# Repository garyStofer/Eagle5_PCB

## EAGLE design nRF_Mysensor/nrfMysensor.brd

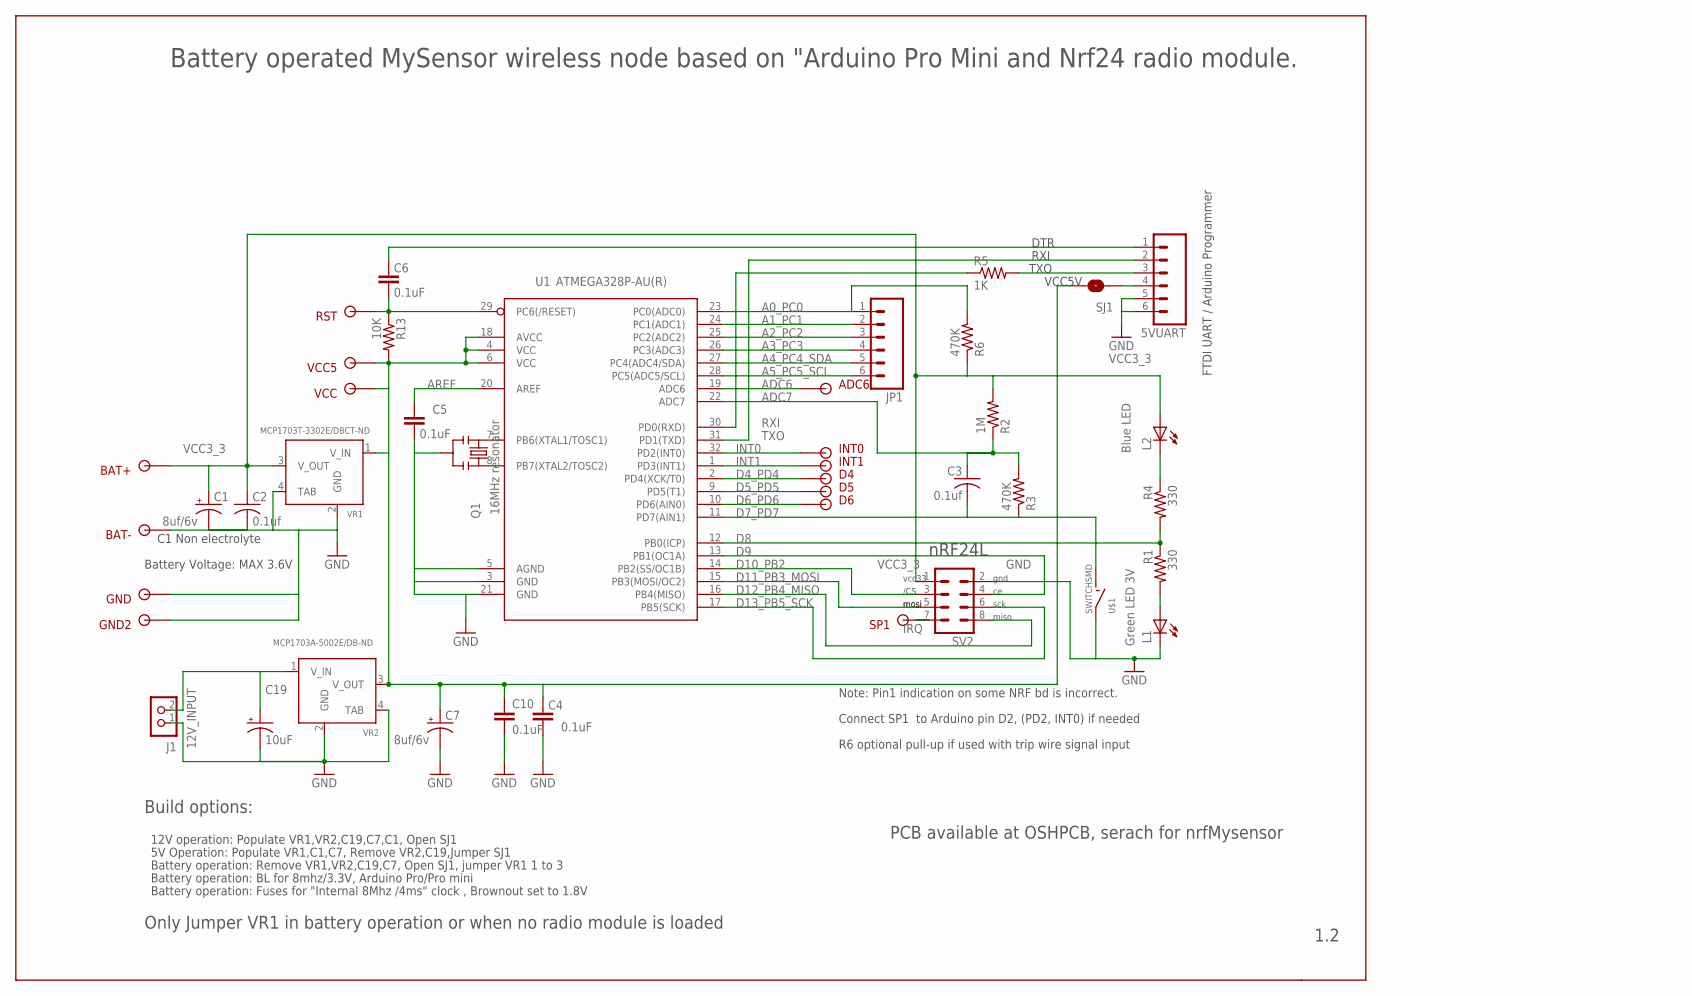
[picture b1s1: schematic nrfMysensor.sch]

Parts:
5VUART: M06SIP; 1X06
ADC6: SOLDER_POINTA; P1-13
BAT+: SOLDER_POINTA; P1-13
BAT-: SOLDER_POINTA; P1-13
C1, C7: 8uf/6v; SMC_B
C2, C3: 0.1uf; C0805
C4, C5, C6, C10: 0.1uF; 0805
C19: 10uF; EIA7343
D4, D5, D6: SOLDER_POINTA; P1-13
GND, GND2: SOLDER_POINTA; P1-13
INT0, INT1: SOLDER_POINTA; P1-13
J1: 12V input; M1X2
JP1: M06SIP; 1X06
L1, L2: LEDSML0603; SML0603
Q1: 16MHz resonator; RESONATOR-SMD
R1, R4: 330; R0603
R2: 1M; R0603
R3, R6: 470K; R0603
R5: 1K; 0603
R13: 10K; 0603
RST: SOLDER_POINTA; P1-13
SJ1: SOLDERJUMPERNO; SJ_2S-NO
SP1: SOLDER_POINTA; P1-13
SV2: MA04-2
U1: ATMEGA328P-AU(R); TQFP32-08
U$1: SWITCHSMD; SMD_SWITCH
VCC, VCC5: SOLDER_POINTA; P1-13
VR1: MCP1703T-3302E/DBCT-ND; SOT223
VR2: MCP1703A-5002E/DB-ND; SOT223

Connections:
5V: C4.2, C7.+, C10.1, R13.2, SJ1.1, U1.4 (VCC), U1.6 (VCC), U1.18 (AVCC), VCC.1, VCC5.1, VR1.1 (V_IN), VR2.3 (V_OUT)
12V_INPUT: C19.A (+), J1.2, VR2.1 (V_IN)
A0_PC0: JP1.1, R6.2, U1.23 (PC0(ADC0))
A1_PC1: JP1.2, U1.24 (PC1(ADC1))
A2_PC2: JP1.3, U1.25 (PC2(ADC2))
A3_PC3: JP1.4, U1.26 (PC3(ADC3))
A4_PC4_SDA: JP1.5, U1.27 (PC4(ADC4/SDA))
A5_PC5_SCL: JP1.6, U1.28 (PC5(ADC5/SCL))
ADC6: ADC6.1, U1.19 (ADC6)
ADC7: C3.1, R2.1, R3.2, U1.22 (ADC7)
AREF: C5.2, U1.20 (AREF)
D4_PD4: D4.1, U1.2 (PD4(XCK/T0))
D5_PD5: D5.1, U1.9 (PD5(T1))
D6_PD6: D6.1, U1.10 (PD6(AIN0))
D7_PD7: C3.2, R3.1, U1.11 (PD7(AIN1)), U$1.P$1
D8: R1.1, R4.2, U1.12 (PB0(ICP))
D9: SV2.4, U1.13 (PB1(OC1A))
D10_PB2: SV2.3, U1.14 (PB2(SS/OC1B))
D11_PB3_MOSI: SV2.5, U1.15 (PB3(MOSI/OC2))
D12_PB4_MISO: SV2.8, U1.16 (PB4(MISO))
D13_PB5_SCK: SV2.6, U1.17 (PB5(SCK))
GND: 5VUART.5, 5VUART.6, BAT-.1, C1.-, C2.2, C4.1, C5.1, C7.-, C10.2, C19.C (-), GND.1, GND2.1, J1.1, L1.C, Q1.2, SV2.2, U1.3 (GND), U1.5 (AGND), U1.21 (GND), U$1.P$2, VR1.2 (GND), VR1.4 (TAB), VR2.2 (GND), VR2.4 (TAB)
INT0: INT0.1, U1.32 (PD2(INT0))
INT1: INT1.1, U1.1 (PD3(INT1))
IRQ: SP1.1, SV2.7
unnamed: L1.A, R1.2
unnamed: L2.C, R4.1
unnamed: 5VUART.3, R5.2
unnamed: 5VUART.4, SJ1.2
unnamed: Q1.1, U1.8 (PB7(XTAL2/TOSC2))
unnamed: 5VUART.1, C6.2
unnamed: Q1.3, U1.7 (PB6(XTAL1/TOSC1))
RESET: C6.1, R13.1, RST.1, U1.29 (PC6(/RESET))
RXI: R5.1, U1.30 (PD0(RXD))
TXO: 5VUART.2, U1.31 (PD1(TXD))
VCC3_3: BAT+.1, C1.+, C2.1, L2.A, R2.2, R6.1, SV2.1, VR1.3 (V_OUT)

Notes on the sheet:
nRF24L
Blue LED
Green LED 3V
Connect SP1 to Arduino pin D2, (PD2, INT0) if needed
Note: Pin1 indication on some NRF bd is incorrect.
/CS
mosi
miso
sck
gnd
vcc33
Battery Voltage: MAX 3.6V
FTDI UART / Arduino Programmer
C1 Non electrolyte
TXO
RXI
VCC5V
DTR
5V Operation: Populate VR1,C1,C7, Remove VR2,C19,Jumper SJ1
12V operation: Populate VR1,VR2,C19,C7,C1, Open SJ1
Battery operation: Remove VR1,VR2,C19,C7, Open SJ1, jumper VR1 1 to 3
Battery operation: BL for 8mhz/3.3V, Arduino Pro/Pro mini
Battery operation: Fuses for "Internal 8Mhz /4ms" clock , Brownout set to 1.8V
1.2
Battery operated MySensor wireless node based on "Arduino Pro Mini and Nrf24 radio module.
Build options:
PCB available at OSHPCB, serach for nrfMysensor
Only Jumper VR1 in battery operation or when no radio module is loaded
R6 optional pull-up if used with trip wire signal input

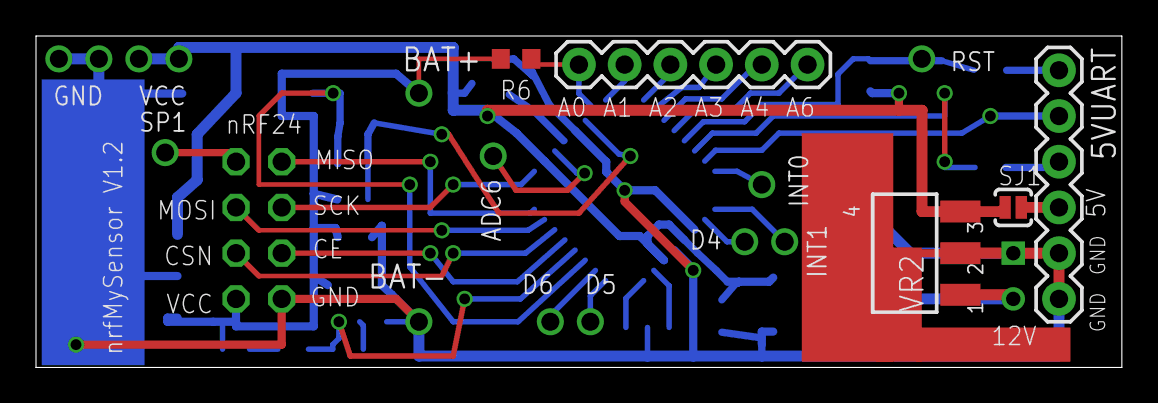
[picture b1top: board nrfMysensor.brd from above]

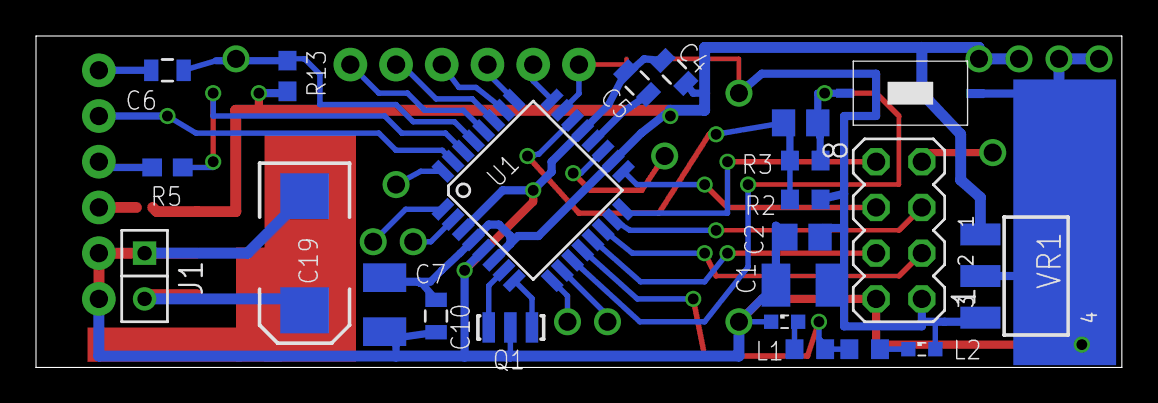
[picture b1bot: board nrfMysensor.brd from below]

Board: 2 copper layers, 60.3 x 18.4 mm, 42 parts (23 on the bottom side), 36 nets.

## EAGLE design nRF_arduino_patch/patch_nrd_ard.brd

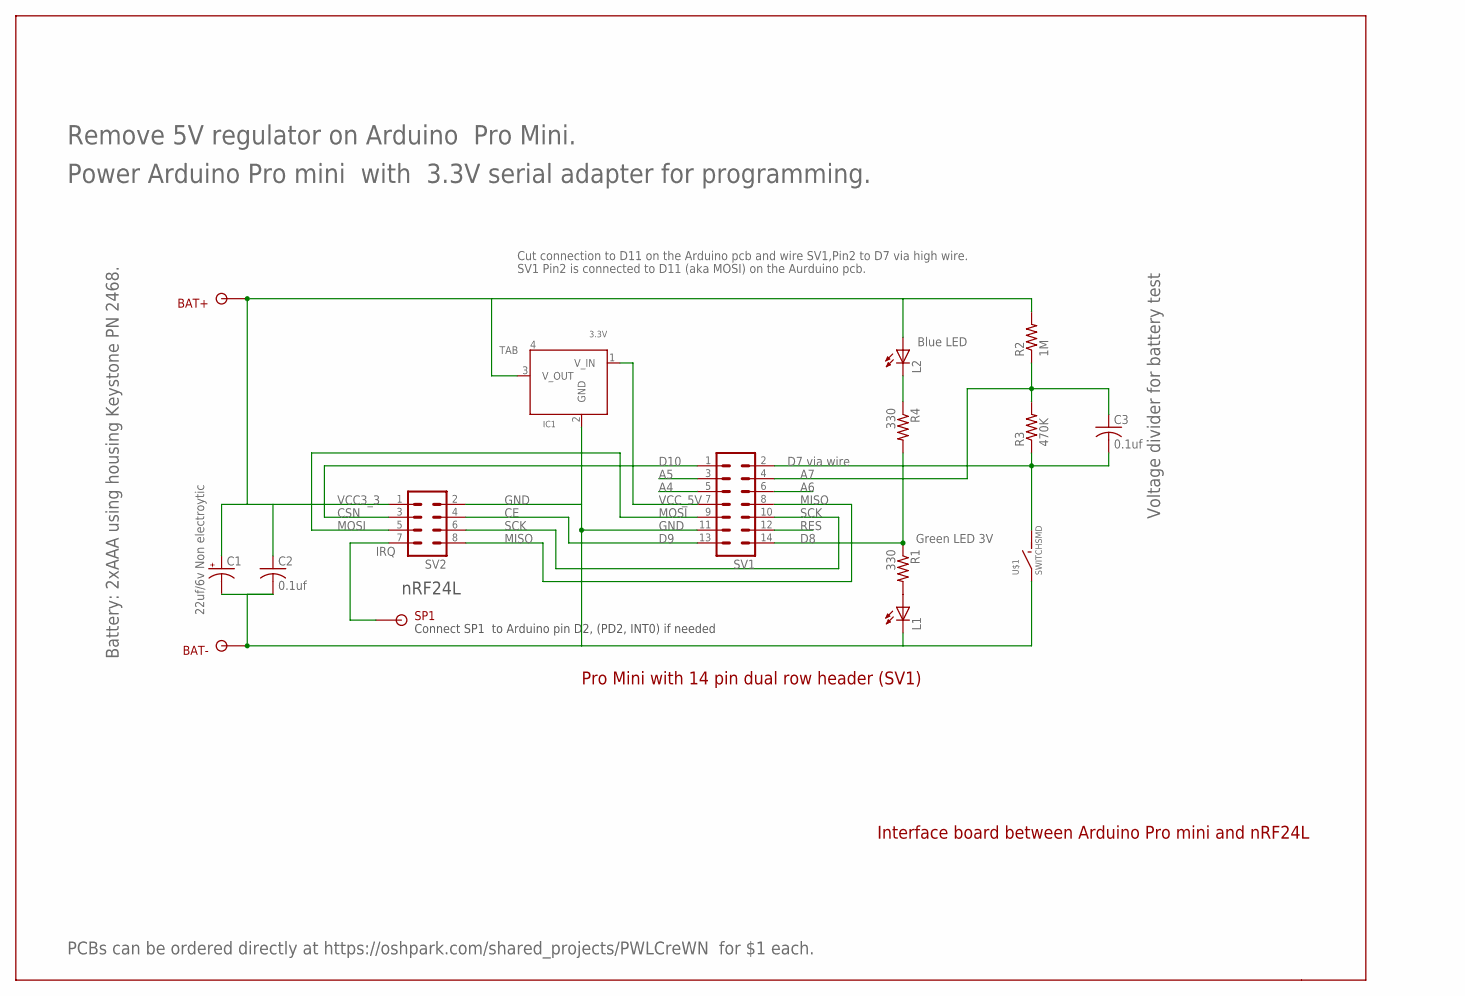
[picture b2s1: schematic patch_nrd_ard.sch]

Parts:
BAT+: SOLDER_POINTA; P1-13
BAT-: SOLDER_POINTA; P1-13
C1: 22uf/6v Non electroytic; SMC_B
C2, C3: 0.1uf; C0805
IC1: 3.3V; SOT223
L1, L2: LEDSML0603; SML0603
R1, R4: 330; R0603
R2: 1M; R0603
R3: 470K; R0603
SP1: SOLDER_POINTA; P1-13
SV1: MA07-2
SV2: MA04-2
U$1: SWITCHSMD; SMD_SWITCH

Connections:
A4: SV1.5
A5: SV1.3
A6: SV1.6
A7: C3.1, R2.1, R3.2, SV1.4
CE: SV1.13, SV2.4
CSN: SV1.1, SV2.3
D8: R1.1, R4.2, SV1.14
D11: C3.2, R3.1, SV1.2, U$1.P$1
GND: BAT-.1, C1.-, C2.2, IC1.2 (GND), L1.C, SV1.11, SV2.2, U$1.P$2
IRQ: SP1.1, SV2.7
MISO: SV1.8, SV2.8
MOSI: SV1.9, SV2.5
unnamed: L1.A, R1.2
unnamed: L2.C, R4.1
RES: SV1.12
SCK: SV1.10, SV2.6
VCC3_3: BAT+.1, C1.+, C2.1, IC1.3 (V_OUT), L2.A, R2.2, SV2.1
VCC_5V: IC1.1 (V_IN), SV1.7

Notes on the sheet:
D10
D7 via wire
Interface board between Arduino Pro mini and nRF24L
Pro Mini with 14 pin dual row header (SV1)
nRF24L
Voltage divider for battery test
Battery: 2xAAA using housing Keystone PN 2468.
Blue LED
Green LED 3V
Cut connection to D11 on the Arduino pcb and wire SV1,Pin2 to D7 via high wire.
SV1 Pin2 is connected to D11 (aka MOSI) on the Aurduino pcb.
PCBs can be ordered directly at https://oshpark.com/shared_projects/PWLCreWN for $1 each.
Remove 5V regulator on Arduino Pro Mini.
Power Arduino Pro mini with 3.3V serial adapter for programming.
Connect SP1 to Arduino pin D2, (PD2, INT0) if needed

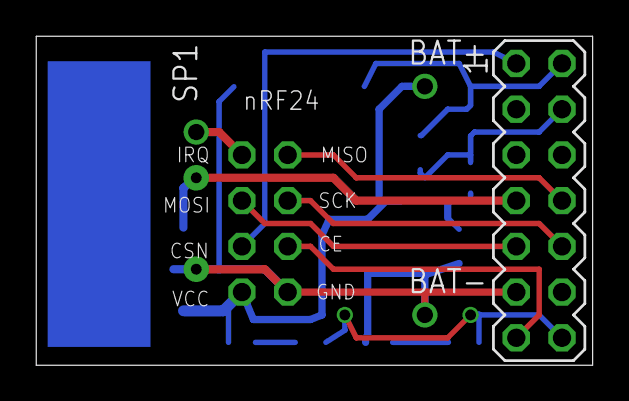
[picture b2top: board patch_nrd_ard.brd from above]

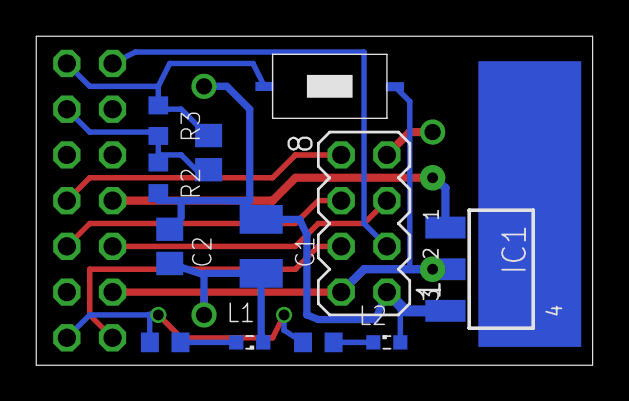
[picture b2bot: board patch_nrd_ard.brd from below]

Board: 2 copper layers, 30.9 x 18.3 mm, 16 parts (12 on the bottom side), 14 nets.

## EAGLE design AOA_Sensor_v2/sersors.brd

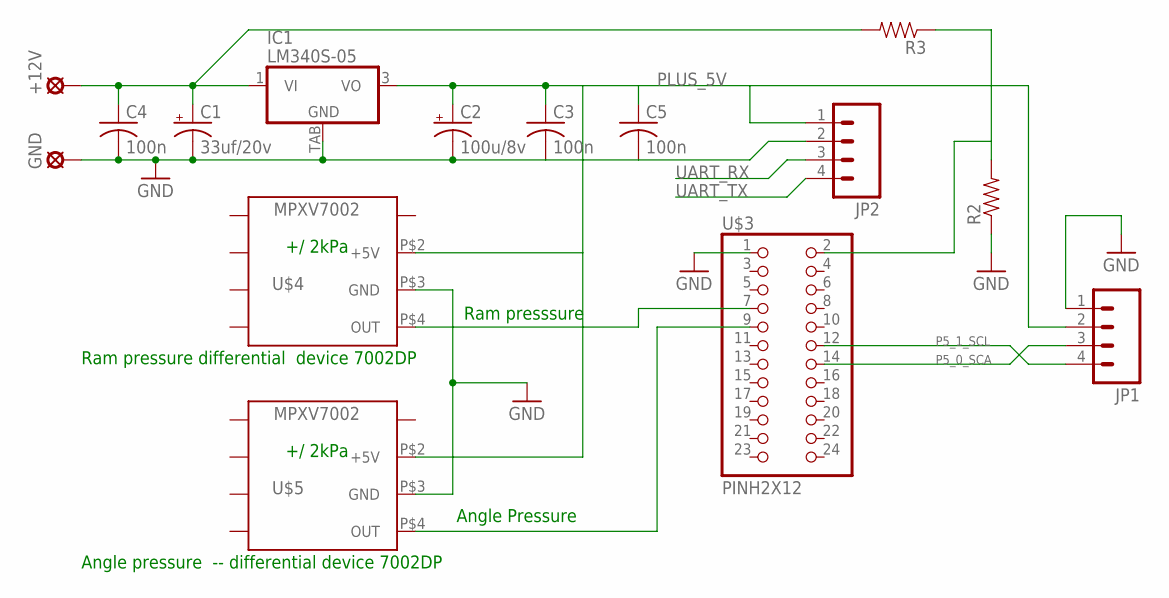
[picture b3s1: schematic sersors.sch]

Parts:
+12V: LSP10
C1: 33uf/20v; SMC_D
C2: 100u/8v; SMC_D
C3, C4, C5: 100n; C1206K
GND: LSP10
IC1: LM340S-05; TO263-3
JP1, JP2: M04PTH; 1X04
R2, R3: RESISTOR0603-RES; 0603-RES
U$3: PINH2X12; 2X12
U$4, U$5: MPXV7002; MPXV

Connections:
GND: C1.-, C2.-, C3.2, C4.2, C5.2, GND.MP, IC1.TAB (GND), JP1.1, JP2.2, R2.1, U$3.1, U$4.P$3 (GND), U$5.P$3 (GND)
unnamed: +12V.MP, C1.+, C4.1, IC1.1 (VI), R3.2
unnamed: U$3.7, U$4.P$4 (OUT)
unnamed: R2.2, R3.1, U$3.2
P3_1: U$3.9, U$5.P$4 (OUT)
P5_0_SCA: JP1.3, U$3.14
P5_1_SCL: JP1.4, U$3.12
PLUS_5V: C2.+, C3.1, C5.1, IC1.3 (VO), JP1.2, JP2.1, U$4.P$2 (+5V), U$5.P$2 (+5V)
UART_RX: JP2.3
UART_TX: JP2.4

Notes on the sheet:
+/ 2kPa
Ram presssure
Angle Pressure
Angle pressure -- differential device 7002DP
Ram pressure differential device 7002DP

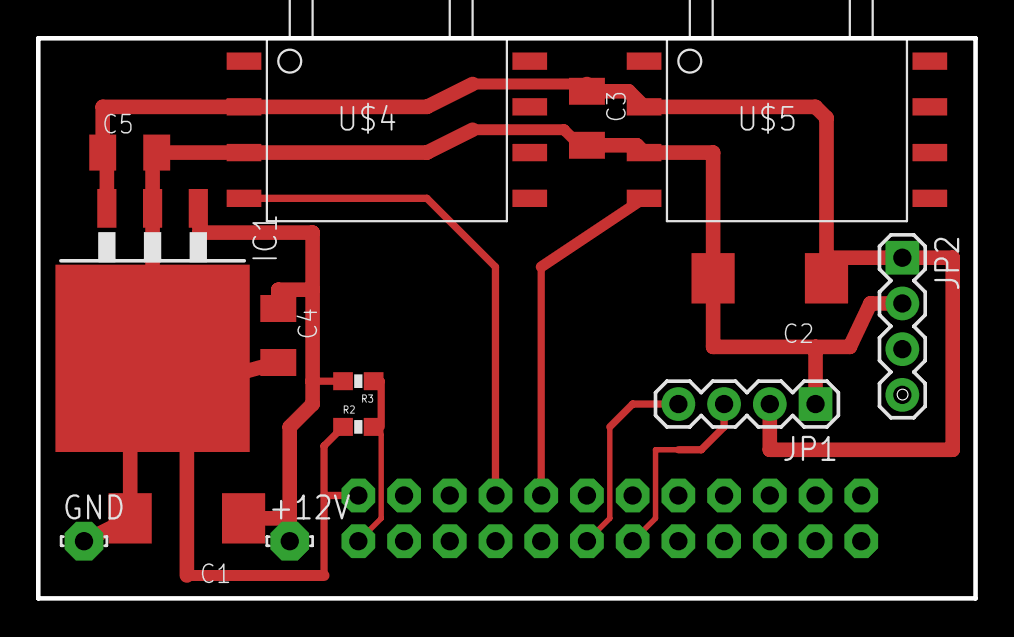
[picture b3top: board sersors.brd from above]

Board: 2 copper layers, 52.1 x 31.1 mm, 15 parts (1 on the bottom side), 8 nets.

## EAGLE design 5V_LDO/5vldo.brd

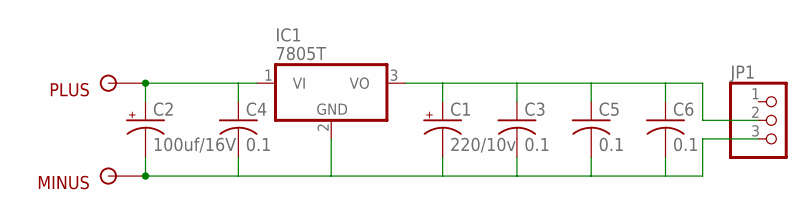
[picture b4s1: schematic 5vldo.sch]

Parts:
C1: 220/10v; SMC_B
C2: 100uf/16V; SMC_B
C3, C4, C5, C6: 0.1; C0805
IC1: 7805T; TO220H
JP1: PINHD-1X3; 1X03
MINUS: SOLDER_POINTD; P1-17Y
PLUS: SOLDER_POINTD; P1-17Y

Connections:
unnamed: C2.+, C4.1, IC1.1 (VI), PLUS.1
unnamed: C1.-, C2.-, C3.2, C4.2, C5.2, C6.2, IC1.2 (GND), JP1.3, MINUS.1
unnamed: C1.+, C3.1, C5.1, C6.1, IC1.3 (VO), JP1.2

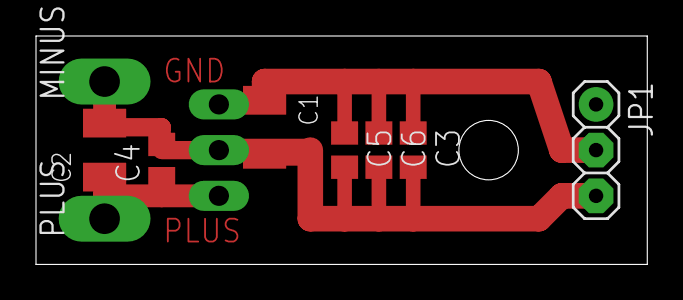
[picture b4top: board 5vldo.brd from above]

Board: 2 copper layers, 34.0 x 12.7 mm, 10 parts (1 on the bottom side), 3 nets.

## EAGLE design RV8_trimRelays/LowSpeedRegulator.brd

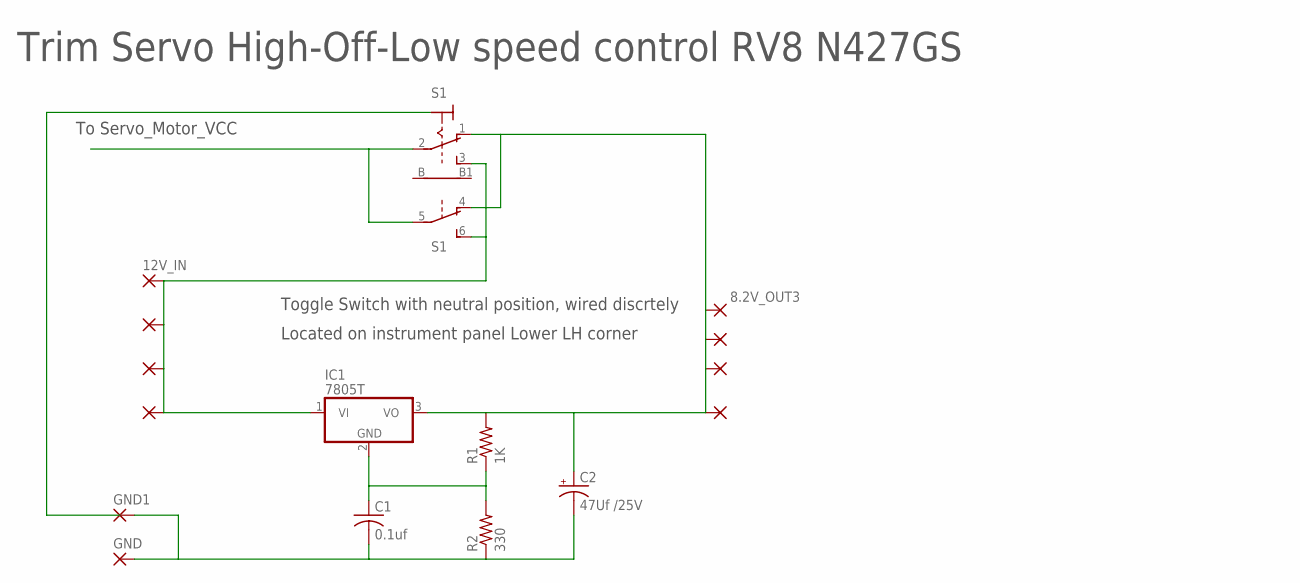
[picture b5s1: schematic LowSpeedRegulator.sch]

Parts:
6V_OUT1, 6V_OUT2, 6V_OUT4, 8.2V_OUT3, 12V, 12V_IN, 12_V, 12_V2: 3,17/1,1
C1: 0.1uf; C0805K
C2: 47Uf /25V; SMC_D
GND, GND1: 3,17/1,1
IC1: 7805T; TO220H
R1: 1K; R0805W
R2: 330; R0805W
S1: 316-923

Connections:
unnamed: C1.1, IC1.2 (GND), R1.1, R2.2
unnamed: C1.2, C2.-, GND.1, GND1.1, R2.1
unnamed: 6V_OUT1.1, 6V_OUT2.1, 6V_OUT4.1, 8.2V_OUT3.1, C2.+, IC1.3 (VO), R1.2, S1.1 (O), S1.4 (O)
unnamed: 12V.1, 12V_IN.1, 12_V.1, 12_V2.1, IC1.1 (VI), S1.3 (S), S1.6 (S)
unnamed: S1.2, S1.5

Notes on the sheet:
To Servo_Motor_VCC
Toggle Switch with neutral position, wired discrtely
Trim Servo High-Off-Low speed control RV8 N427GS
Located on instrument panel Lower LH corner

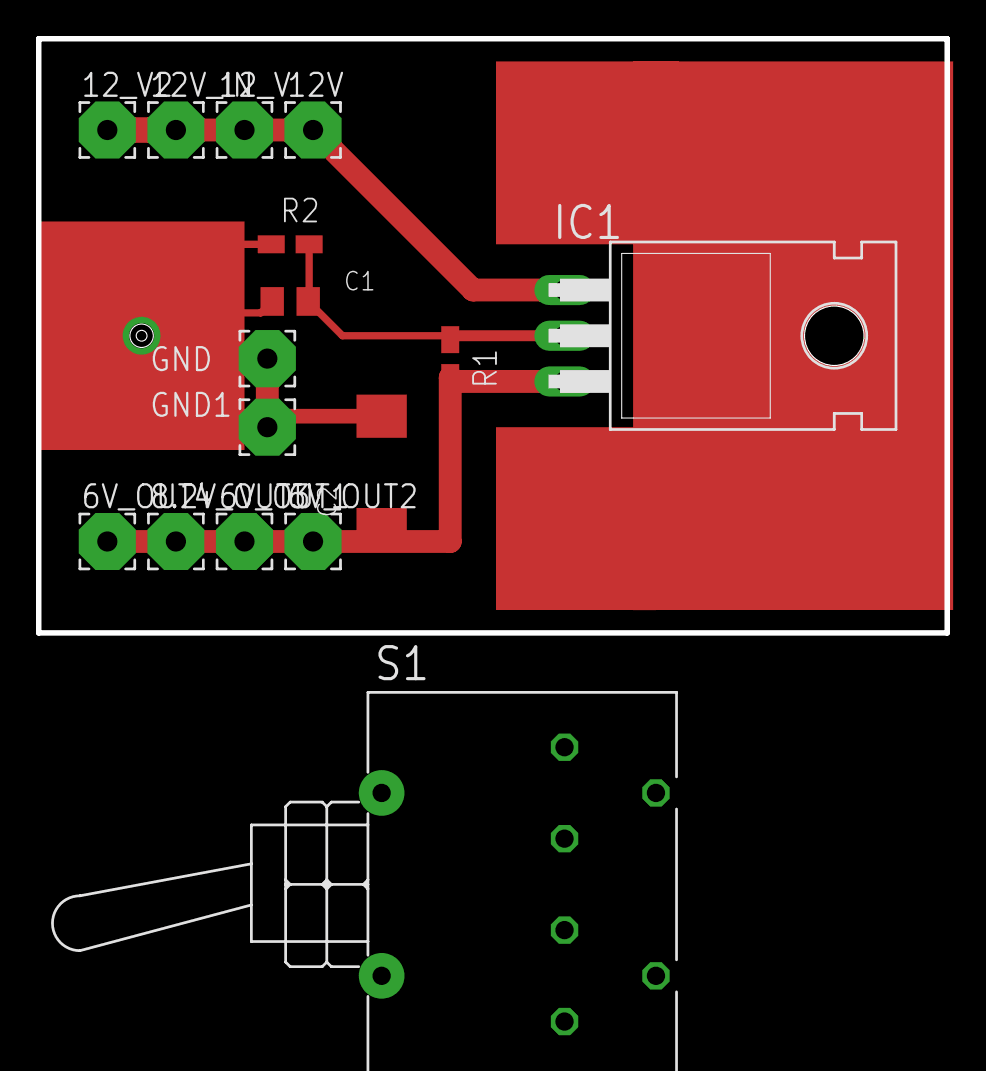
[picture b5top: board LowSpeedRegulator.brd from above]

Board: 2 copper layers, 50.5 x 33.0 mm, 16 parts (0 on the bottom side), 5 nets.

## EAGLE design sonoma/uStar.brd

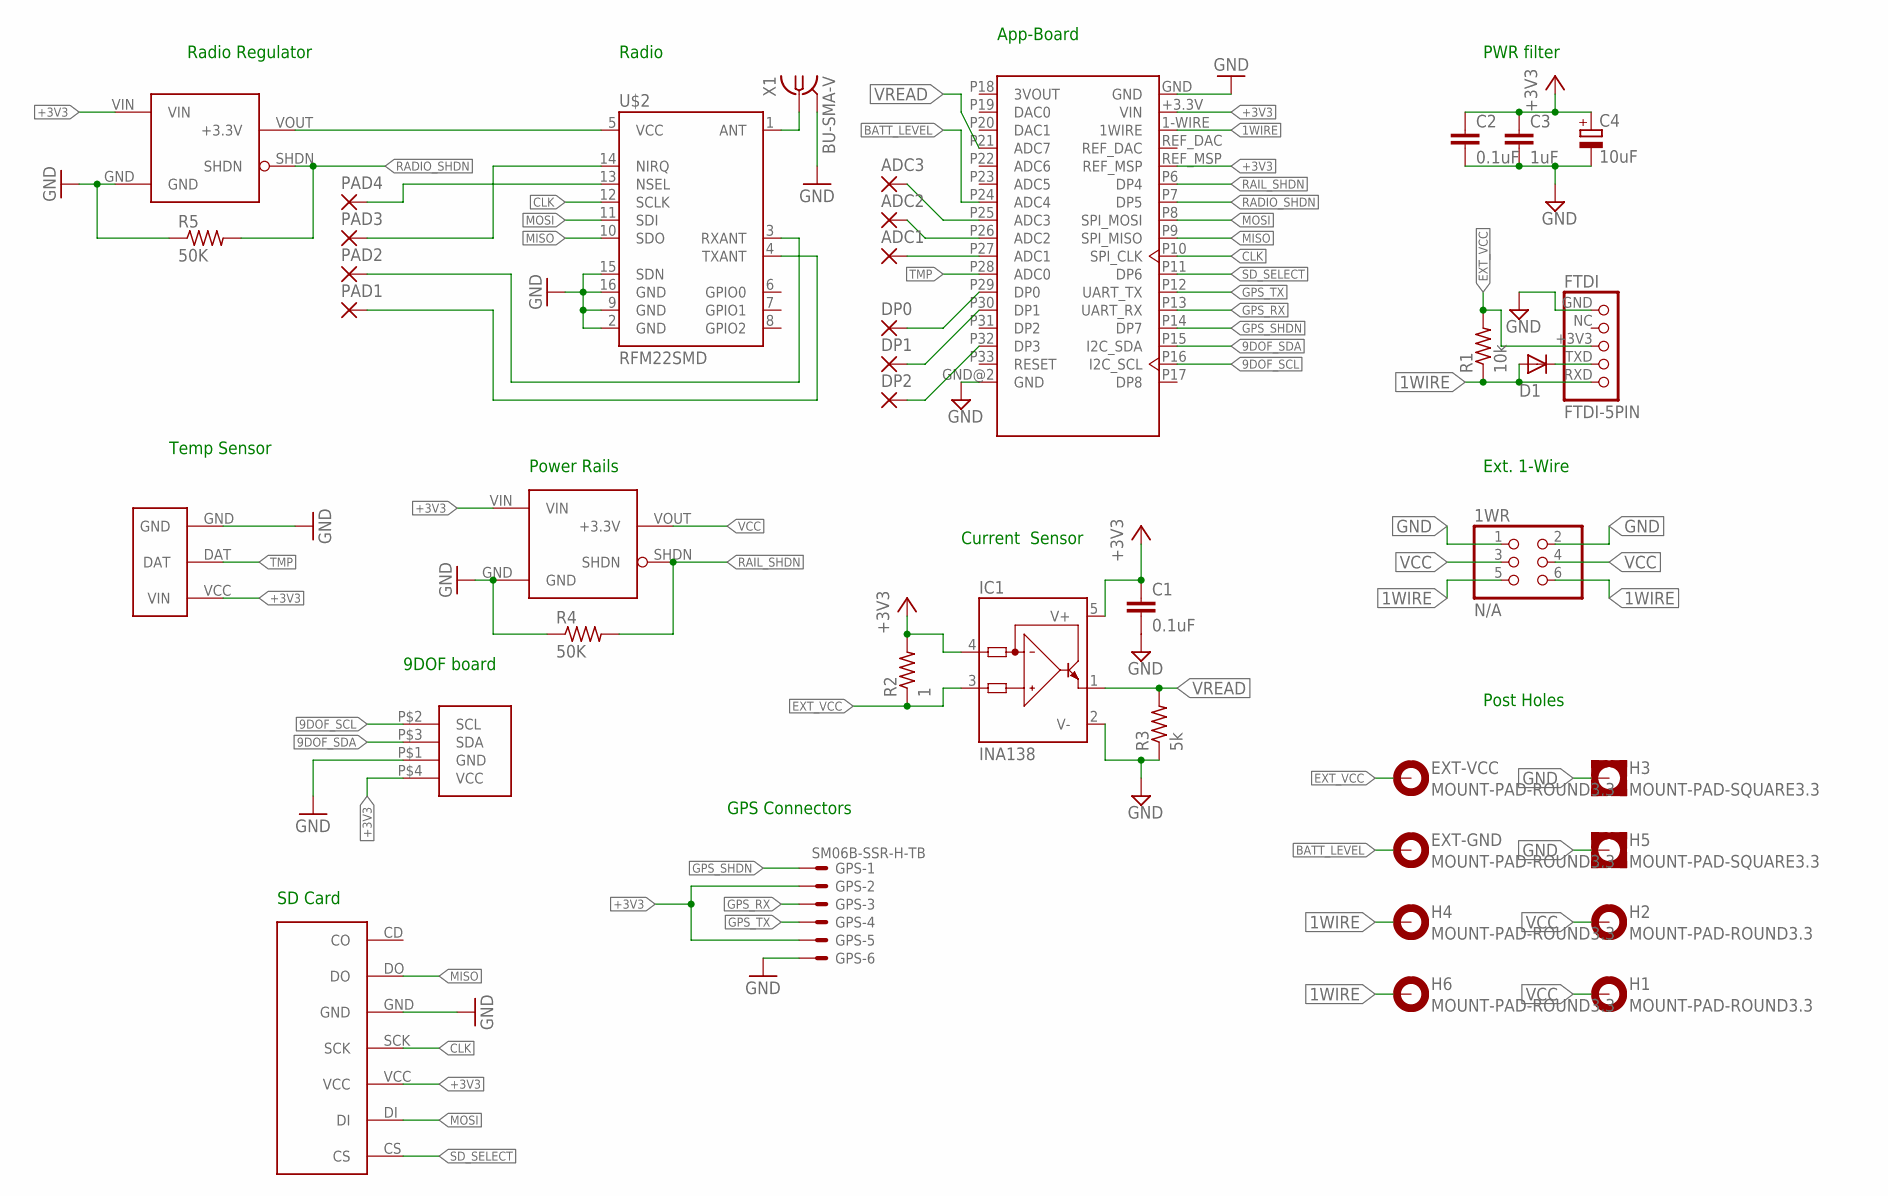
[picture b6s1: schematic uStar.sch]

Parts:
1WR: N/A; 2X03
ADC1, ADC2, ADC3: 1,6/0,9
C1: 0.1uF; C0805
C2: 0.1uF; C0603
C3: 1uF; C0603
C4: 10uF; SMC_B
D1: 1N4148DO35-7; DO35-7
DP0, DP1, DP2: 1,6/0,9
EXT-GND: MOUNT-PAD-ROUND3.3; 3,3-PAD
EXT-VCC: MOUNT-PAD-ROUND3.3; 3,3-PAD
FTDI: FTDI-5PIN; 1_05X2MM
GPS: SM06B-SSR-H-TB
H1, H2, H4, H6: MOUNT-PAD-ROUND3.3; 3,3-PAD
H3, H5: MOUNT-PAD-SQUARE3.3; 3,3-PAD-SQUARE
IC1: INA138; SOT23-5
PAD1, PAD2, PAD3, PAD4: 1,6/0,9
R1: 10k; 0207/7
R2: 1; R0603
R3: 5k; R0603
R4, R5: 50K; R0603
U$1: App-Board 1.2/1.3; APPCORE_RECEIVER
U$2: RFM22SMD; RFM22-XXX-S2
U$3, U$7: S7V8F3_VOLT_REG-3V3_1AHORZ-DOWN; S7V_DOWN
U$4: TMP_EXT
U$5: 9DOF
U$6: SDCARD_EXT
X1: BU-SMA-V

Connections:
1WIRE: 1WR.5, 1WR.6, D1.A, FTDI.RXD, H4.B3,3, H6.B3,3, R1.1, U$1.1-WIRE (1WIRE)
9DOF_SCL: U$1.P16 (I2C_SCL), U$5.P$2 (SCL)
9DOF_SDA: U$1.P15 (I2C_SDA), U$5.P$3 (SDA)
+3V3: C1.1, C2.1, C3.1, C4.+, GPS.2, GPS.5, IC1.4 (IN-), IC1.5 (V+), R2.2, U$1.+3.3V (VIN), U$1.REF_MSP, U$3.VIN, U$4.VCC (VIN), U$5.P$4 (VCC), U$6.VCC, U$7.VIN
BATT_LEVEL: EXT-GND.B3,3, U$1.P24 (ADC4)
CLK: U$1.P10 (SPI_CLK), U$2.12 (SCLK), U$6.SCK
EXT_VCC: EXT-VCC.B3,3, FTDI.+3V3, IC1.3 (IN+), R1.2, R2.1
GND: 1WR.1, 1WR.2, C1.2, C2.2, C3.2, C4.-, FTDI.GND, GPS.6, H3.B3,3, H5.B3,3, IC1.2 (V-), R3.1, R4.1, R5.1, U$1.GND, U$1.GND@2 (GND), U$2.2 (GND), U$2.9 (GND), U$2.15 (SDN), U$2.16 (GND), U$3.GND, U$4.GND, U$5.P$1 (GND), U$6.GND, U$7.GND, X1.2, X1.3 (2), X1.4 (2), X1.5 (2)
GPS_RX: GPS.3, U$1.P13 (UART_RX)
GPS_SHDN: GPS.1, U$1.P14 (DP7)
GPS_TX: GPS.4, U$1.P12 (UART_TX)
MISO: U$1.P9 (SPI_MISO), U$2.10 (SDO), U$6.DO
MOSI: U$1.P8 (SPI_MOSI), U$2.11 (SDI), U$6.DI
unnamed: PAD1.1, U$2.4 (TXANT)
unnamed: PAD2.1, U$2.3 (RXANT)
unnamed: D1.C, FTDI.TXD
unnamed: PAD3.1, U$2.14 (NIRQ)
unnamed: PAD4.1, U$2.13 (NSEL)
unnamed: U$2.1 (ANT), X1.1
unnamed: U$2.5 (VCC), U$3.VOUT (+3.3V)
unnamed: ADC1.1, U$1.P27 (ADC1)
unnamed: ADC2.1, U$1.P26 (ADC2)
unnamed: ADC3.1, U$1.P25 (ADC3)
unnamed: DP0.1, U$1.P29 (DP0)
unnamed: DP1.1, U$1.P30 (DP1)
unnamed: DP2.1, U$1.P32 (DP3)
RADIO_SHDN: R5.2, U$1.P7 (DP5), U$3.SHDN
RAIL_SHDN: R4.2, U$1.P6 (DP4), U$7.SHDN
SD_SELECT: U$1.P11 (DP6), U$6.CS
TMP: U$1.P28 (ADC0), U$4.DAT
VCC: 1WR.3, 1WR.4, H1.B3,3, H2.B3,3, U$7.VOUT (+3.3V)
VREAD: IC1.1 (OUT), R3.2, U$1.P21 (ADC7)

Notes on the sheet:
Post Holes
Ext. 1-Wire
App-Board
PWR filter
Current Sensor
Radio
Radio Regulator
Temp Sensor
9DOF board
GPS Connectors
SD Card
Power Rails

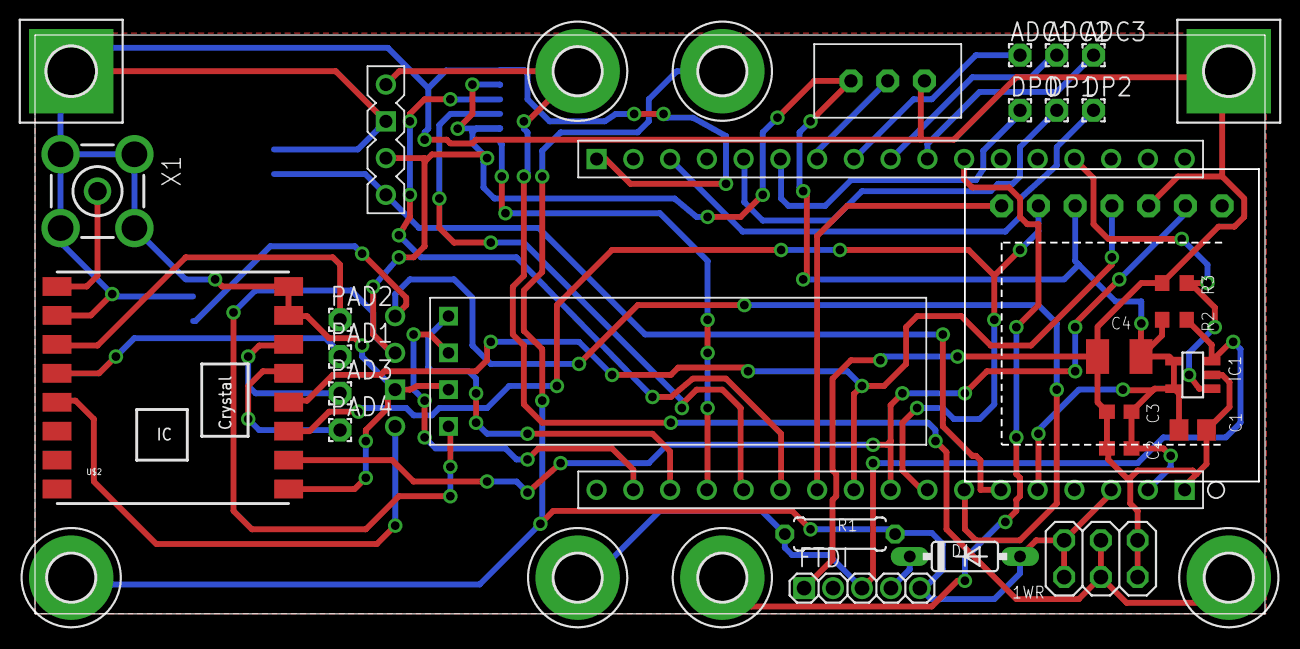
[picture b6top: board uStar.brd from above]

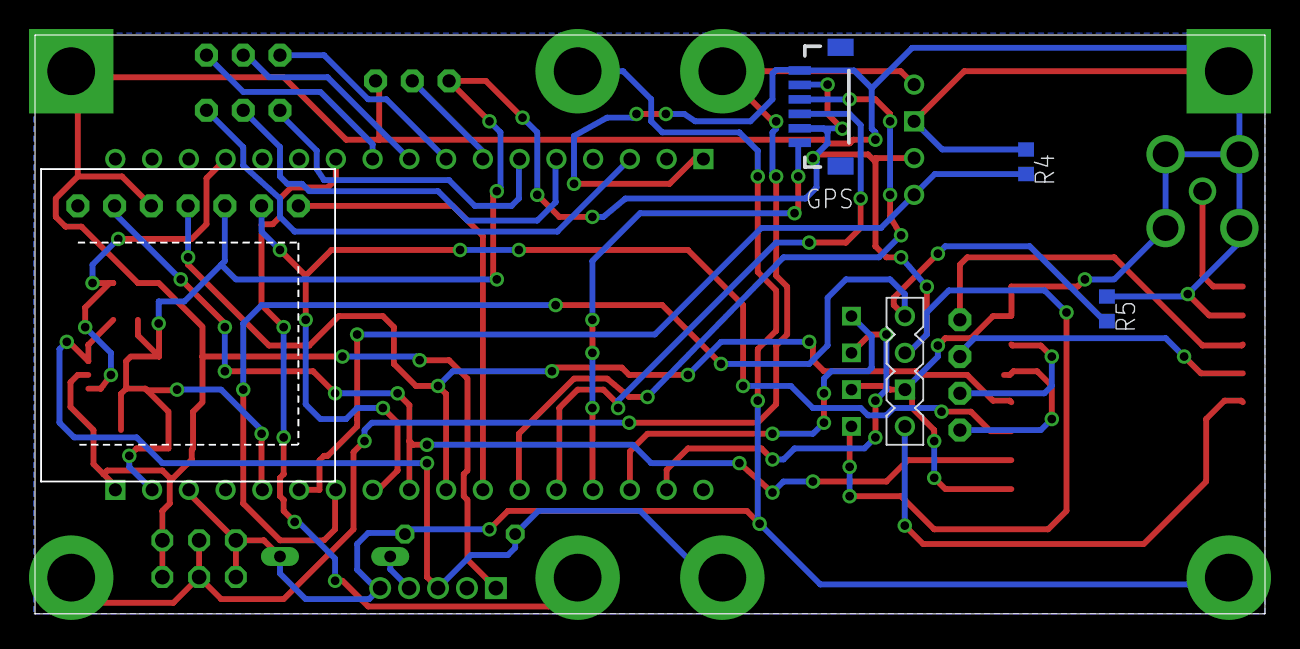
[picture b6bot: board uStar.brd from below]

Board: 2 copper layers, 85.0 x 40.0 mm, 40 parts (5 on the bottom side), 32 nets.

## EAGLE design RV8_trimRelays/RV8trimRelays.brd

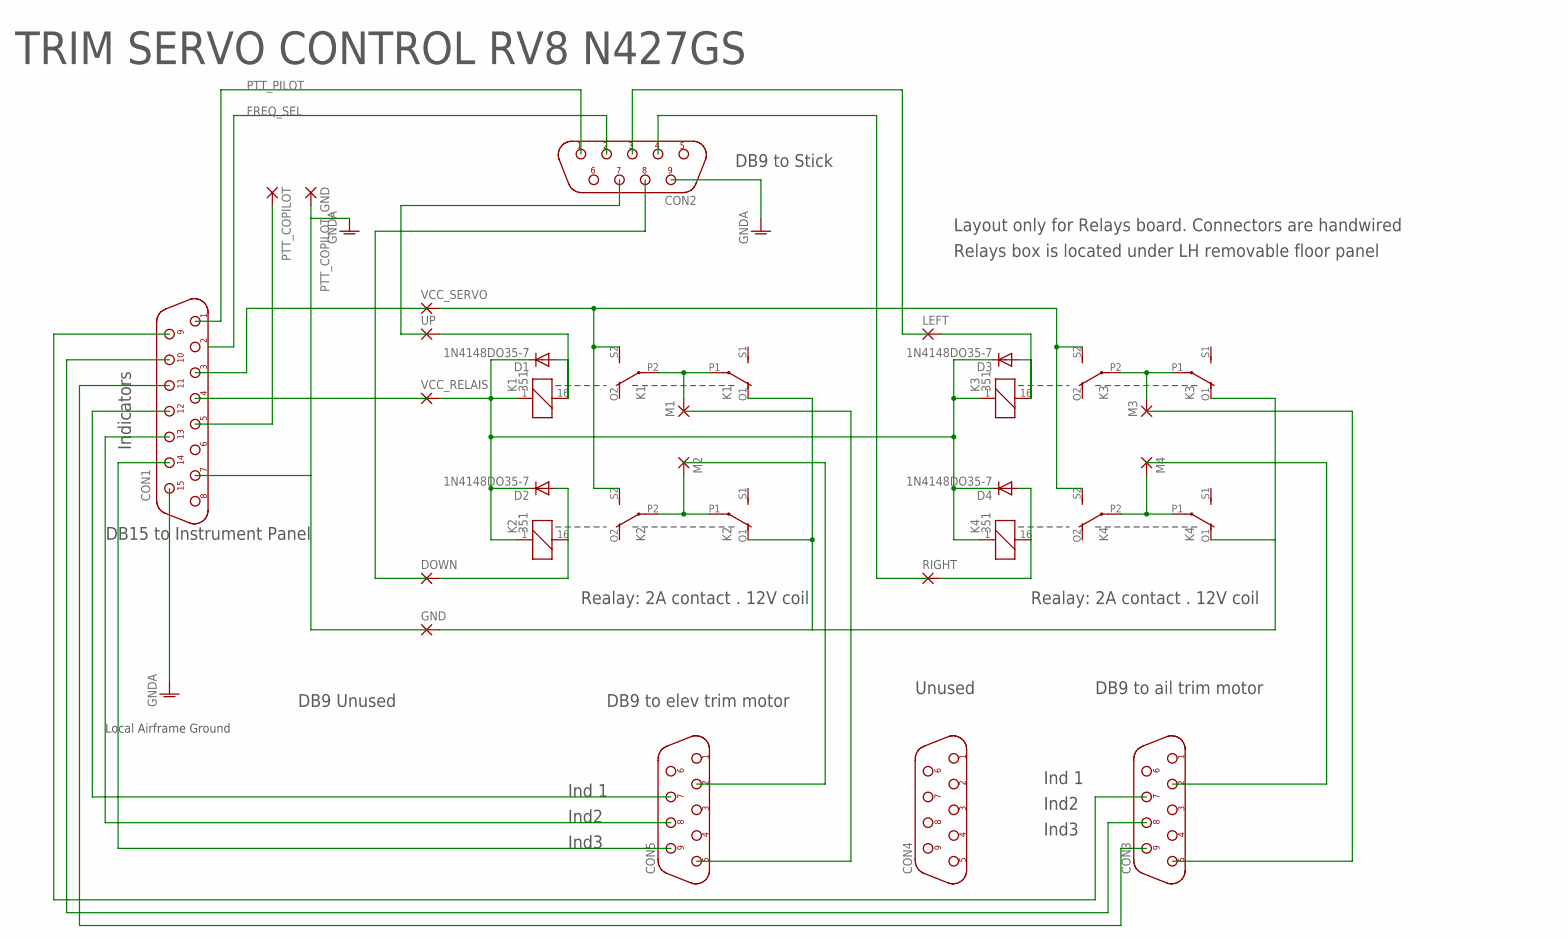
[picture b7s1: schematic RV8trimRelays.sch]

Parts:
CON1: DB15F; D-15F
CON2, CON3, CON4, CON5: DB9F; D-09F
D1, D2, D3, D4: 1N4148DO35-7; DO35-7
DOWN: 2,15/1,0
GND: 2,15/1,0
K1, K2, K3, K4: 351
LEFT: 2,15/1,0
M1, M2, M3, M4: 2,15/1,0
PTT_COPILOT: 2,15/1,0
PTT_COPILOT_GND: 2,15/1,0
RIGHT: 2,15/1,0
UP: 2,15/1,0
VCC_RELAIS: 2,15/1,0
VCC_SERVO: 2,15/1,0

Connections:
FREQ_SEL: CON2.2
GNDA: CON1.7, CON1.15, CON2.9, PTT_COPILOT_GND.1
unnamed: K2.P1, K2.P2, M2.1
unnamed: K1.S2 (S), K2.S2 (S), K3.S2 (S), K4.S2 (S), VCC_SERVO.1
unnamed: D2.A, DOWN.1, K2.16 (2)
unnamed: K1.P1, K1.P2, M1.1
unnamed: GND.1, K1.O1 (O), K2.O1 (O), K3.O1 (O), K4.O1 (O)
unnamed: D1.C, D2.C, D3.C, D4.C, K1.1, K2.1, K3.1, K4.1, VCC_RELAIS.1
unnamed: D1.A, K1.16 (2), UP.1
unnamed: K3.P1, K3.P2, M3.1
unnamed: D3.A, K3.16 (2), LEFT.1
unnamed: K4.P1, K4.P2, M4.1
unnamed: D4.A, K4.16 (2), RIGHT.1
unnamed: CON1.9, CON3.7
unnamed: CON1.10, CON3.8
unnamed: CON1.11, CON3.9
unnamed: CON1.12, CON5.7
unnamed: CON1.13, CON5.8
unnamed: CON1.14, CON5.9
PTT_COPILOT: CON1.5, PTT_COPILOT.1
PTT_PILOT: CON1.1, CON2.1

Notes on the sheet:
Local Airframe Ground
DB15 to Instrument Panel
DB9 to Stick
DB9 to elev trim motor
DB9 to ail trim motor
DB9 Unused
Indicators
Ind 1
Ind2
Ind3
Unused
Layout only for Relays board. Connectors are handwired
Relays box is located under LH removable floor panel
TRIM SERVO CONTROL RV8 N427GS
Realay: 2A contact . 12V coil

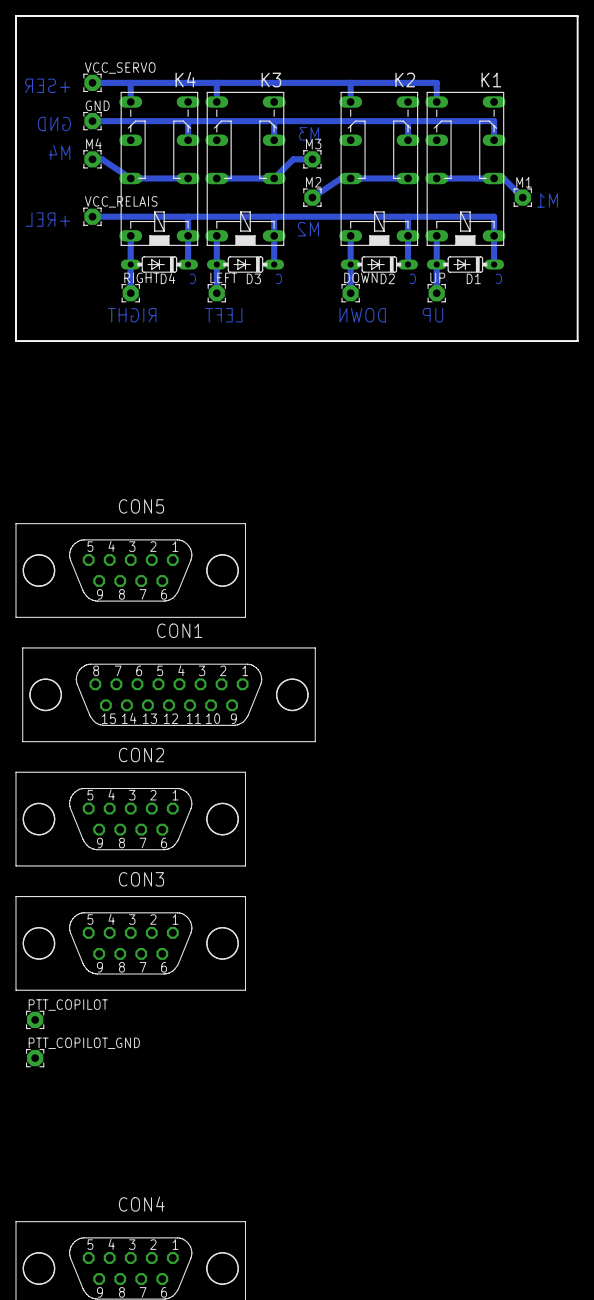
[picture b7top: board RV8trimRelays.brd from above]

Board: 2 copper layers, 74.6 x 43.2 mm, 26 parts (0 on the bottom side), 20 nets.

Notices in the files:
parts and their libraries:
SparkFun-Connectors: Licensing: CC v3.0 Share-Alike You are welcome to use this library for commercial purposes.
